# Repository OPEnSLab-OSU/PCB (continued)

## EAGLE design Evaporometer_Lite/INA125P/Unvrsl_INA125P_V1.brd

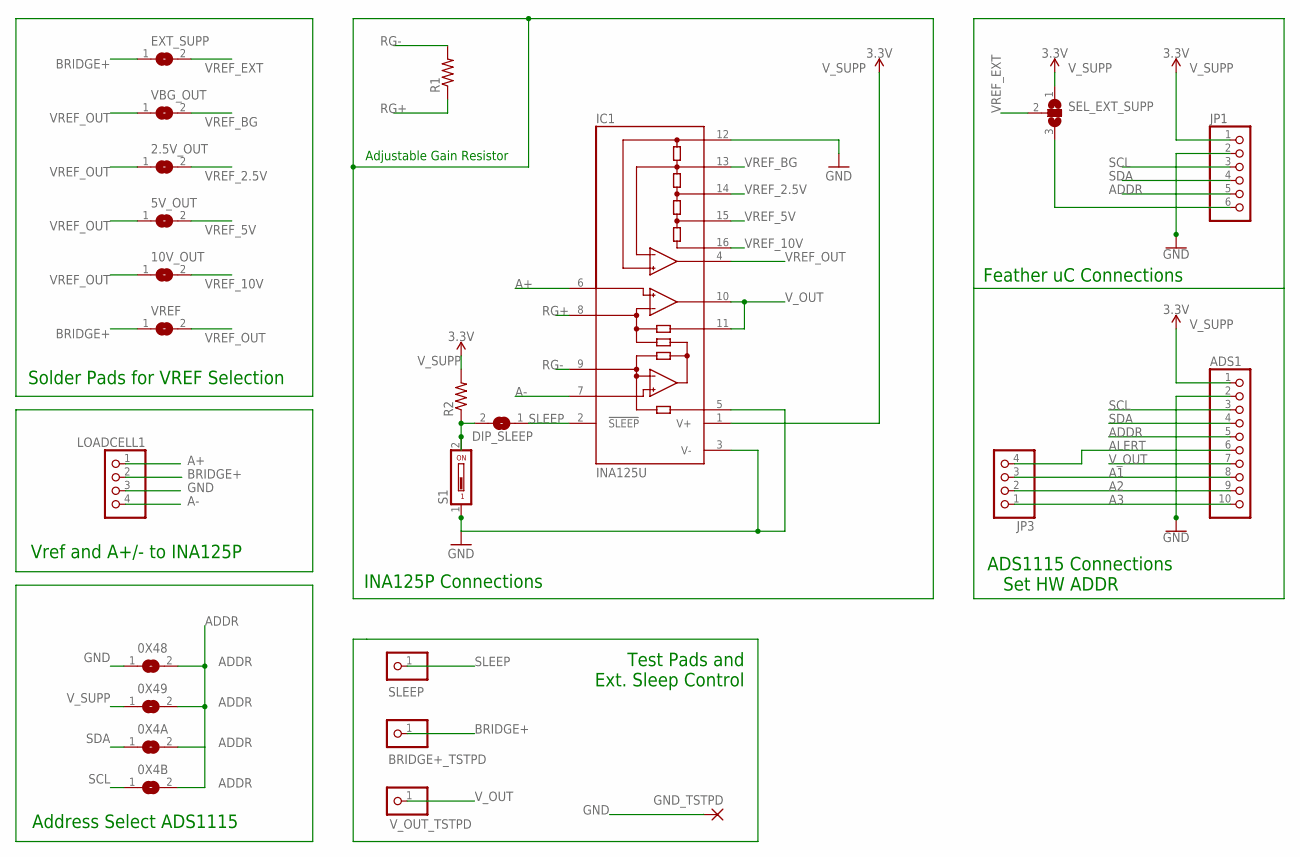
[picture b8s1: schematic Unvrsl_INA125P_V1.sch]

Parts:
0X4A, 0X4B, 0X48, 0X49, 2.5V_OUT, 5V_OUT, 10V_OUT: SJ
ADS1: PINHD-1X10; 1X10
BRIDGE+_TSTPD: PINHD-1X1; 1X01
DIP_SLEEP: SJ
EXT_SUPP: SJ
GND_TSTPD: WIREPADSMD2,54-5,08; SMD2,54-5,08
IC1: INA125U; SO16-1
JP1: PINHD-1X6; 1X06
JP3: PINHD-1X4; 1X04
LOADCELL1: PINHD-1X4; 1X04
R1: R-US_R0603; R0603
R2: R-US_R1206; R1206
S1: DS01; DS-01
SEL_EXT_SUPP: SJ2WW; SJ_2W
SLEEP: PINHD-1X1; 1X01
VBG_OUT: SJ
VREF: SJ
V_OUT_TSTPD: PINHD-1X1; 1X01

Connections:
A1: ADS1.8, JP3.3
A2: ADS1.9, JP3.2
A3: ADS1.10, JP3.1
A+: IC1.6 (+IN), LOADCELL1.1
A-: IC1.7 (-IN), LOADCELL1.4
ADDR: 0X4A.2, 0X4B.2, 0X48.2, 0X49.2, ADS1.5, JP1.5
ALERT: ADS1.6, JP3.4
BRIDGE+: BRIDGE+_TSTPD.1, EXT_SUPP.1, LOADCELL1.2, VREF.1
GND: 0X48.1, ADS1.2, GND_TSTPD.1, IC1.3 (V-), IC1.5 (REF), IC1.12 (REFCOM), JP1.2, LOADCELL1.3, S1.1
unnamed: JP1.6, SEL_EXT_SUPP.3
unnamed: DIP_SLEEP.2, R2.1, S1.2
RG+: IC1.8 (RG), R1.1
RG-: IC1.9 (RG), R1.2
SCL: 0X4B.1, ADS1.3, JP1.3
SDA: 0X4A.1, ADS1.4, JP1.4
SLEEP: DIP_SLEEP.1, IC1.2 (!SLEEP), SLEEP.1
VREF_2.5V: 2.5V_OUT.2, IC1.14 (REF2.5)
VREF_5V: 5V_OUT.2, IC1.15 (REF5)
VREF_10V: 10V_OUT.2, IC1.16 (REF10)
VREF_BG: IC1.13 (REFBG), VBG_OUT.2
VREF_EXT: EXT_SUPP.2, SEL_EXT_SUPP.2
VREF_OUT: 2.5V_OUT.1, 5V_OUT.1, 10V_OUT.1, IC1.4 (REFOUT), VBG_OUT.1, VREF.2
V_OUT: ADS1.7, IC1.10 (OUT), IC1.11 (SENSE), V_OUT_TSTPD.1
V_SUPP: 0X49.1, ADS1.1, IC1.1 (V+), JP1.1, R2.2, SEL_EXT_SUPP.1

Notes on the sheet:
Vref and A+/- to INA125P
Solder Pads for VREF Selection
Feather uC Connections
Address Select ADS1115
ADS1115 Connections Set HW ADDR
Adjustable Gain Resistor
INA125P Connections
Test Pads and Ext. Sleep Control

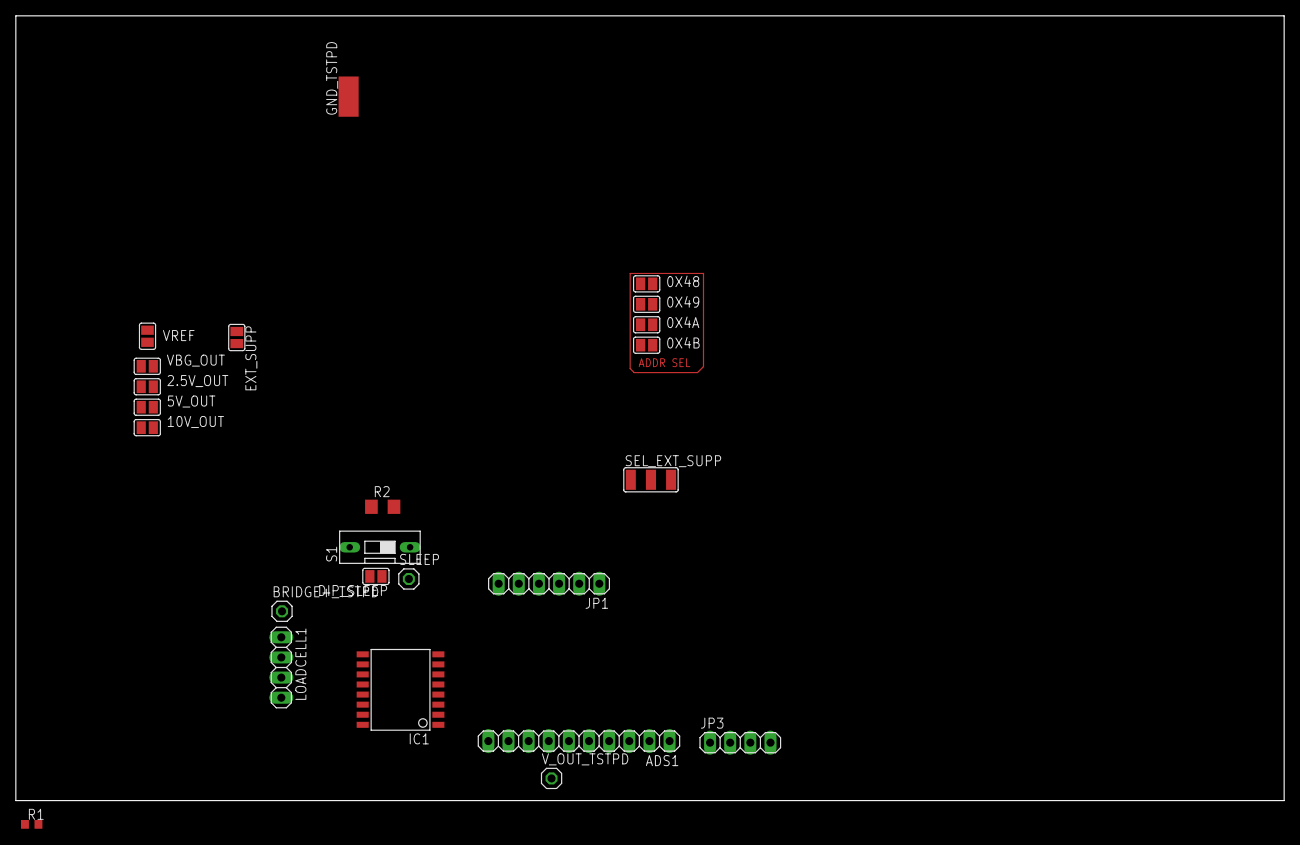
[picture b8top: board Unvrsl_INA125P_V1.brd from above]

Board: 2 copper layers, 160.0 x 99.0 mm, 24 parts (0 on the bottom side), 24 nets.

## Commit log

2020-02-03 Initial links for eagle files
2020-02-03 fixed links
2020-02-21 Rename sapflow_v3.brd to Sapflow/sapflow_v3.brd
2020-02-22 initial commit example :)
2020-02-23 Added new flex probe
2020-02-23 added smart probe files
2020-02-29 Sync with laser cutter computer files
2020-03-03 updated w/ front page READMe
2020-03-03 "restore files"
2020-03-03 Normalized all line endings
2020-03-12 Made flex probe thinner
    Also made a panel layout, so we can fit more PCBs into the same area.
2020-03-19 added v2 of smart probe in Sapflow
2020-03-20 added sapflow wing v4
2020-03-20 Removed duplicate versions
2020-03-20 Removed sapflow board v3
2020-03-20 Created BOM for orders of 12 boards
    Reduced the BOM length by changing some part values on sapflow_v4
2020-04-09 Added hardware tests
2020-04-24 changed to v5 of sapflow wing
2020-07-21 Added feather schematic to OPEnS_Library
2020-07-21 Schematic can now be included without package
